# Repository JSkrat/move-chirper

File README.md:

# move-chirper
Movement sensor to announce movement with audible chirps

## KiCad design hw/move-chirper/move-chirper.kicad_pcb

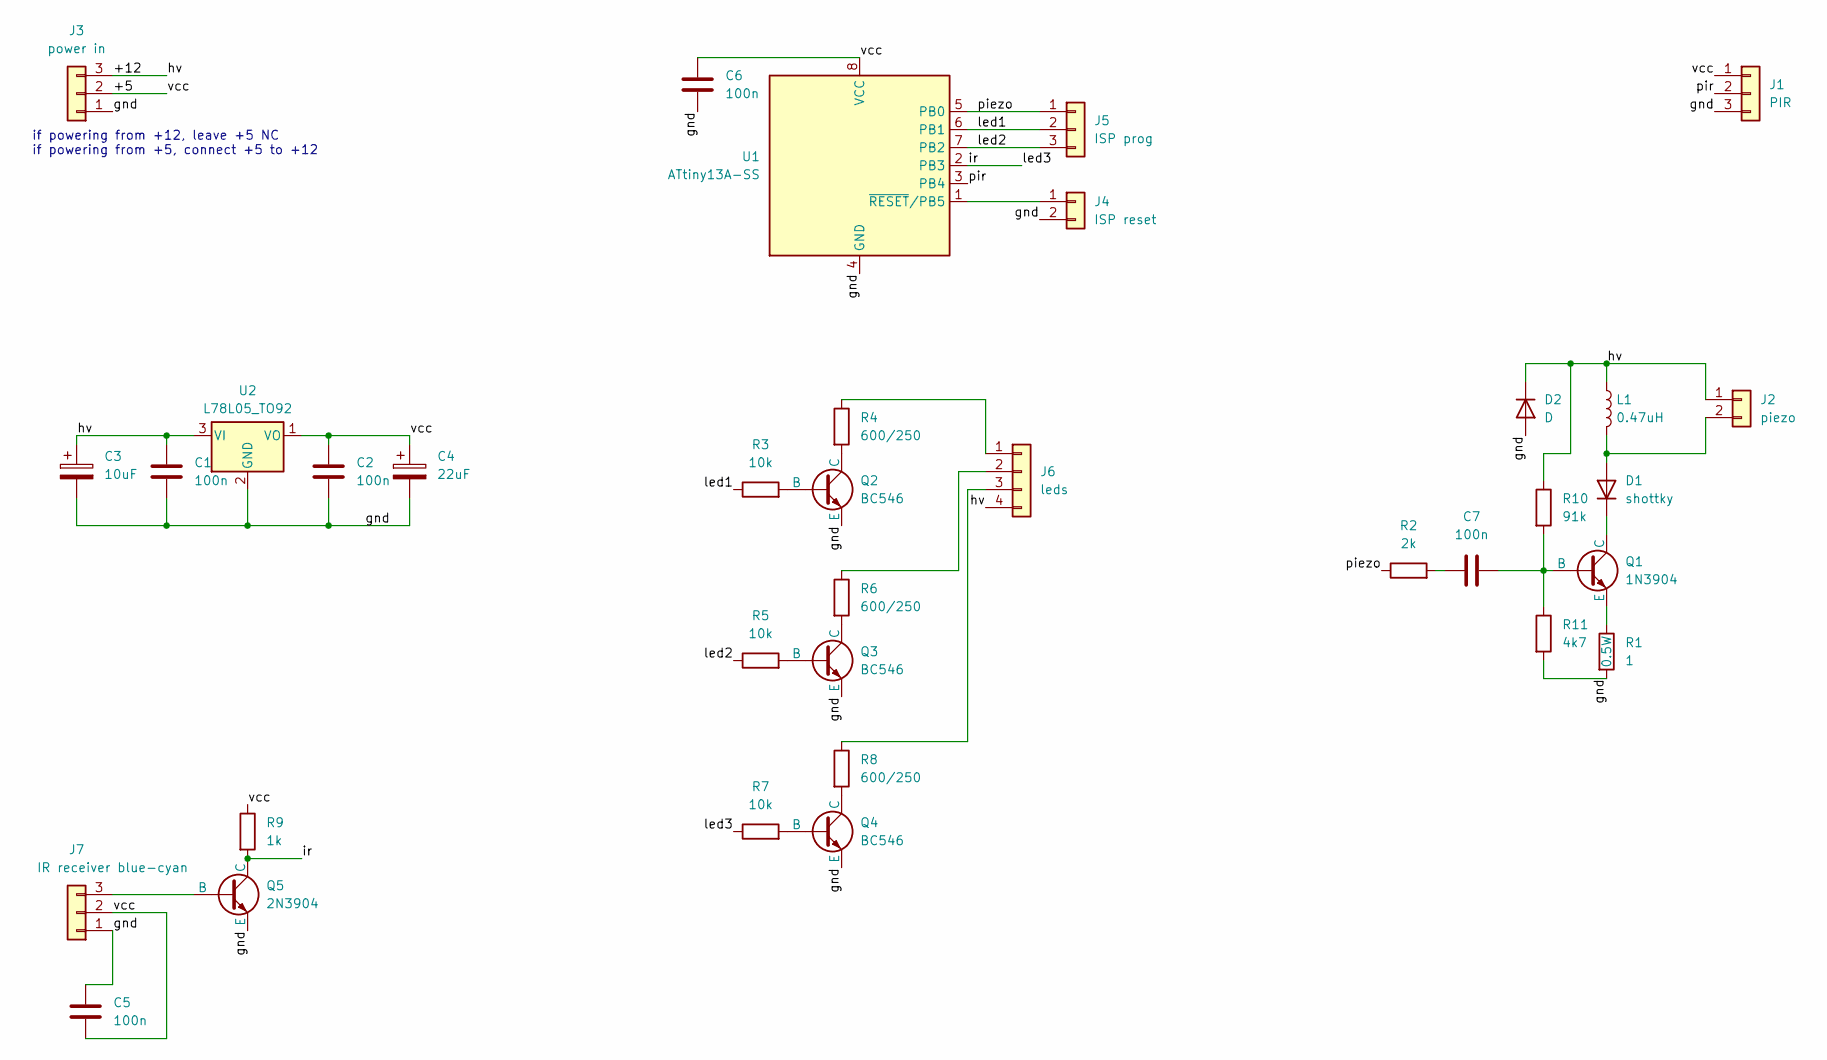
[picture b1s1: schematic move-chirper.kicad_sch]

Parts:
C1, C2, C5, C6, C7: 100n; C_Disc_D5.0mm_W2.5mm_P2.50mm
C3: 10uF; CP_Radial_D4.0mm_P2.00mm
C4: 22uF; CP_Radial_D6.3mm_P2.50mm
D1: shottky; D_A-405_P10.16mm_Horizontal
D2: D; D_A-405_P10.16mm_Horizontal
J1: PIR; PinHeader_1x03_P2.54mm_Vertical
J2: piezo; PinHeader_1x02_P2.54mm_Vertical
J3: power in; PinHeader_1x03_P2.54mm_Vertical
J4: ISP reset; PinHeader_1x02_P2.54mm_Vertical
J5: ISP prog; PinHeader_1x03_P2.54mm_Vertical
J6: leds; PinHeader_1x04_P2.54mm_Vertical
J7: IR receiver blue-cyan; PinHeader_1x03_P2.54mm_Vertical
L1: 0.47uH; L_Radial_D10.5mm_P5.00mm_Abacron_AISR-01
Q1: 1N3904; TO-92L_Inline_Wide
Q2, Q3, Q4: BC546; TO-92L_Inline_Wide
Q5: 2N3904; TO-92L_Inline_Wide
R1: 1; R_Axial_DIN0309_L9.0mm_D3.2mm_P15.24mm_Horizontal
R2: 2k; R_Axial_DIN0207_L6.3mm_D2.5mm_P10.16mm_Horizontal
R3, R5, R7: 10k; R_Axial_DIN0207_L6.3mm_D2.5mm_P10.16mm_Horizontal
R4, R6, R8: 600/250; R_Axial_DIN0207_L6.3mm_D2.5mm_P10.16mm_Horizontal
R9: 1k; R_Axial_DIN0207_L6.3mm_D2.5mm_P10.16mm_Horizontal
R10: 91k; R_Axial_DIN0207_L6.3mm_D2.5mm_P10.16mm_Horizontal
R11: 4k7; R_Axial_DIN0207_L6.3mm_D2.5mm_P10.16mm_Horizontal
U1: ATtiny13A-SS; DIP-8_W7.62mm
U2: L78L05_TO92; TO-92_Inline_Wide

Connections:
/+5: C2.1, C4.1, C5.2, C6.1, J1.1, J3.2, J7.2, R9.1, U1.8 (VCC), U2.1 (VO)
/+12: C1.1, C3.1, D2.1 (K), J2.1, J3.3, J6.4, L1.1, R10.1, U2.3 (VI)
/gnd: C1.2, C2.2, C3.2, C4.2, C5.1, C6.2, D2.2 (A), J1.3, J3.1, J4.2, J7.1, Q2.3 (E), Q3.3 (E), Q4.3 (E), Q5.3 (E), R1.2, R11.2, U1.4 (GND), U2.2 (GND)
/ir: Q5.1 (C), R7.1, R9.2, U1.2 (PB3)
/led1: J5.2, R3.1, U1.6 (PB1)
/led2: J5.3, R5.1, U1.7 (PB2)
/piezo: J5.1, R2.1, U1.5 (PB0)
/pir: J1.2, U1.3 (PB4)
unnamed: C7.1, R2.2
unnamed: D1.2 (A), J2.2, L1.2
unnamed: D1.1 (K), Q1.1 (C)
unnamed: J4.1, U1.1 (~RESET/PB5)
unnamed: J6.1, R4.1
unnamed: J6.2, R6.1
unnamed: J6.3, R8.1
unnamed: J7.3, Q5.2 (B)
unnamed: C7.2, Q1.2 (B), R10.2, R11.1
unnamed: Q1.3 (E), R1.1
unnamed: Q2.2 (B), R3.2
unnamed: Q2.1 (C), R4.2
unnamed: Q3.2 (B), R5.2
unnamed: Q3.1 (C), R6.2
unnamed: Q4.2 (B), R7.2
unnamed: Q4.1 (C), R8.2

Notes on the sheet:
if powering from +12, leave +5 NC if powering from +5, connect +5 to +12

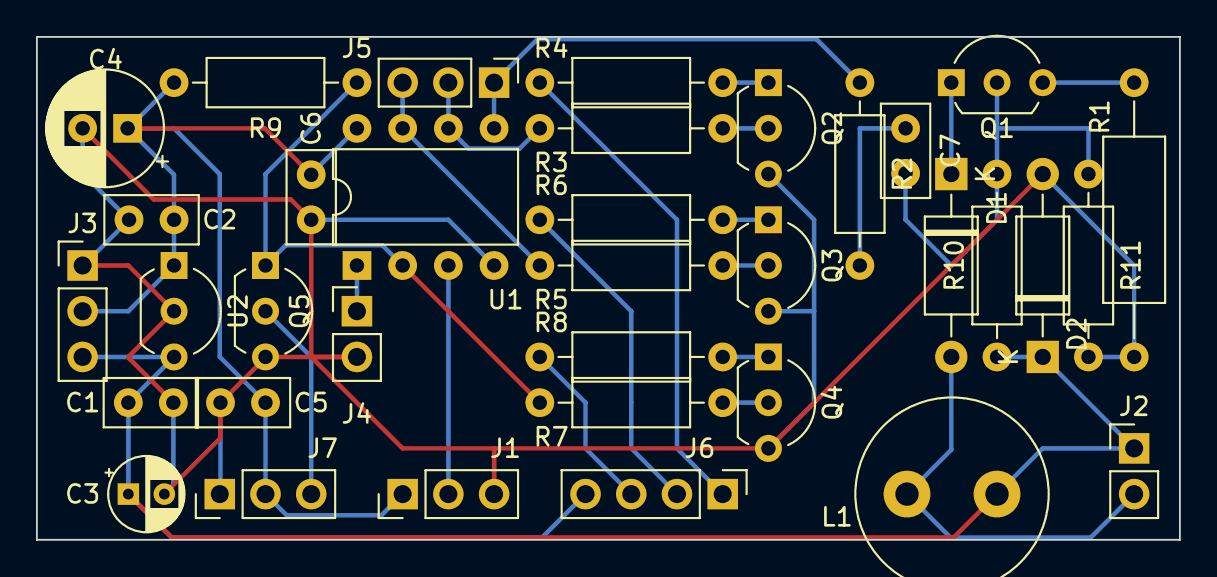
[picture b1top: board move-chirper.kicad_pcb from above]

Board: 2 copper layers, 63.5 x 27.9 mm, 35 parts (0 on the bottom side), 24 nets.

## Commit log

2025-08-06 add scheme
2025-08-12 wip: casing created all modules
2025-09-03 add firmware project
2025-09-03 fw: init-2)
2025-09-19 hw update
